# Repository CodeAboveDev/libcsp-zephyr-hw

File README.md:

# Cubesat Space Protocol with Zephyr - Hardware
PCB schematic and layout for stacking WeAct BlackPill boards.

Software: https://github.com/CodeAboveDev/libcsp-zephyr

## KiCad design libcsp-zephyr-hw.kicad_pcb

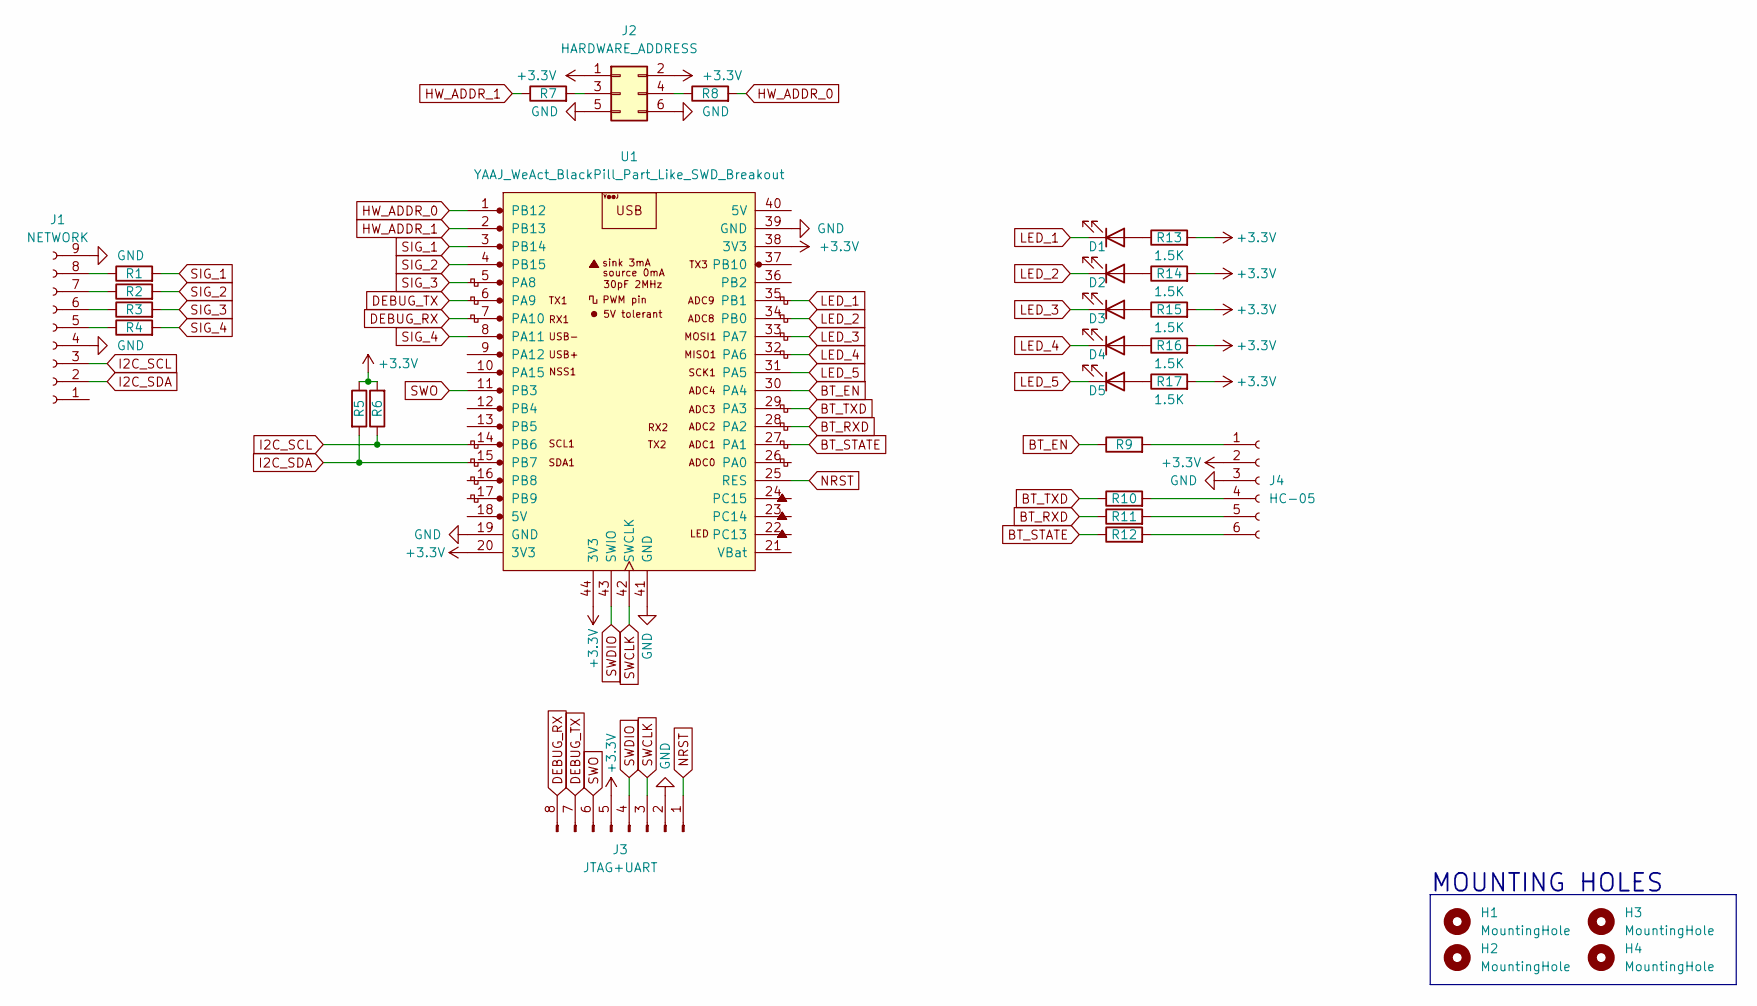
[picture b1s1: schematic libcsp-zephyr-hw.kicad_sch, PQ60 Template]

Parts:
D1, D2, D3, D4, D5: LED; LED_0805_2012Metric
H1, H2, H3, H4: MountingHole; MountingHole_2.2mm_M2_Pad_Via
J1: NETWORK; PinSocket_1x09_P2.54mm_Vertical
J2: HARDWARE_ADDRESS; PinHeader_2x03_P2.54mm_Horizontal
J3: JTAG+UART; PinHeader_1x08_P2.54mm_Horizontal
J4: HC-05; PinSocket_1x06_P2.54mm_Vertical
R1, R2, R3, R4, R5, R6, R7, R8, R9, R10, R11, R12: R; R_0805_2012Metric
R13, R14, R15, R16, R17: 1.5K; R_0805_2012Metric
U1: YAAJ_WeAct_BlackPill_Part_Like_SWD_Breakout; YAAJ_WeAct_BlackPill_SWD_2

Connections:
+3.3V: J2.1, J2.2, J3.5, J4.2, R5.1, R6.2, R13.2, R14.2, R15.2, R16.2, R17.2, U1.20 (3V3), U1.38 (3V3), U1.44 (3V3)
BT_EN: R9.1, U1.30 (PA4)
BT_RXD: R11.1, U1.28 (PA2)
BT_STATE: R12.1, U1.27 (PA1)
BT_TXD: R10.1, U1.29 (PA3)
DEBUG_RX: J3.8, U1.7 (PA10)
DEBUG_TX: J3.7, U1.6 (PA9)
GND: J1.4, J1.9, J2.5, J2.6, J3.2, J4.3, U1.19 (GND), U1.39 (GND), U1.41 (GND)
HW_ADDR_0: R8.2, U1.1 (PB12)
HW_ADDR_1: R7.1, U1.2 (PB13)
I2C_SCL: J1.3, R6.1, U1.14 (PB6)
I2C_SDA: J1.2, R5.2, U1.15 (PB7)
LED_1: D1.1 (K), U1.35 (PB1)
LED_2: D2.1 (K), U1.34 (PB0)
LED_3: D3.1 (K), U1.33 (PA7)
LED_4: D4.1 (K), U1.32 (PA6)
LED_5: D5.1 (K), U1.31 (PA5)
NRST: J3.1, U1.25 (RES)
unnamed: D1.2 (A), R13.1
unnamed: D2.2 (A), R14.1
unnamed: D3.2 (A), R15.1
unnamed: D4.2 (A), R16.1
unnamed: D5.2 (A), R17.1
unnamed: J1.5, R4.1
unnamed: J1.6, R3.1
unnamed: J1.7, R2.1
unnamed: J1.8, R1.1
unnamed: J2.3, R7.2
unnamed: J2.4, R8.1
unnamed: J4.1, R9.2
unnamed: J4.4, R10.2
unnamed: J4.5, R11.2
unnamed: J4.6, R12.2
SIG_1: R1.2, U1.3 (PB14)
SIG_2: R2.2, U1.4 (PB15)
SIG_3: R3.2, U1.5 (PA8)
SIG_4: R4.2, U1.8 (PA11)
SWCLK: J3.3, U1.42 (SWCLK)
SWDIO: J3.4, U1.43 (SWIO)
SWO: J3.6, U1.11 (PB3)

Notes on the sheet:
MOUNTING HOLES

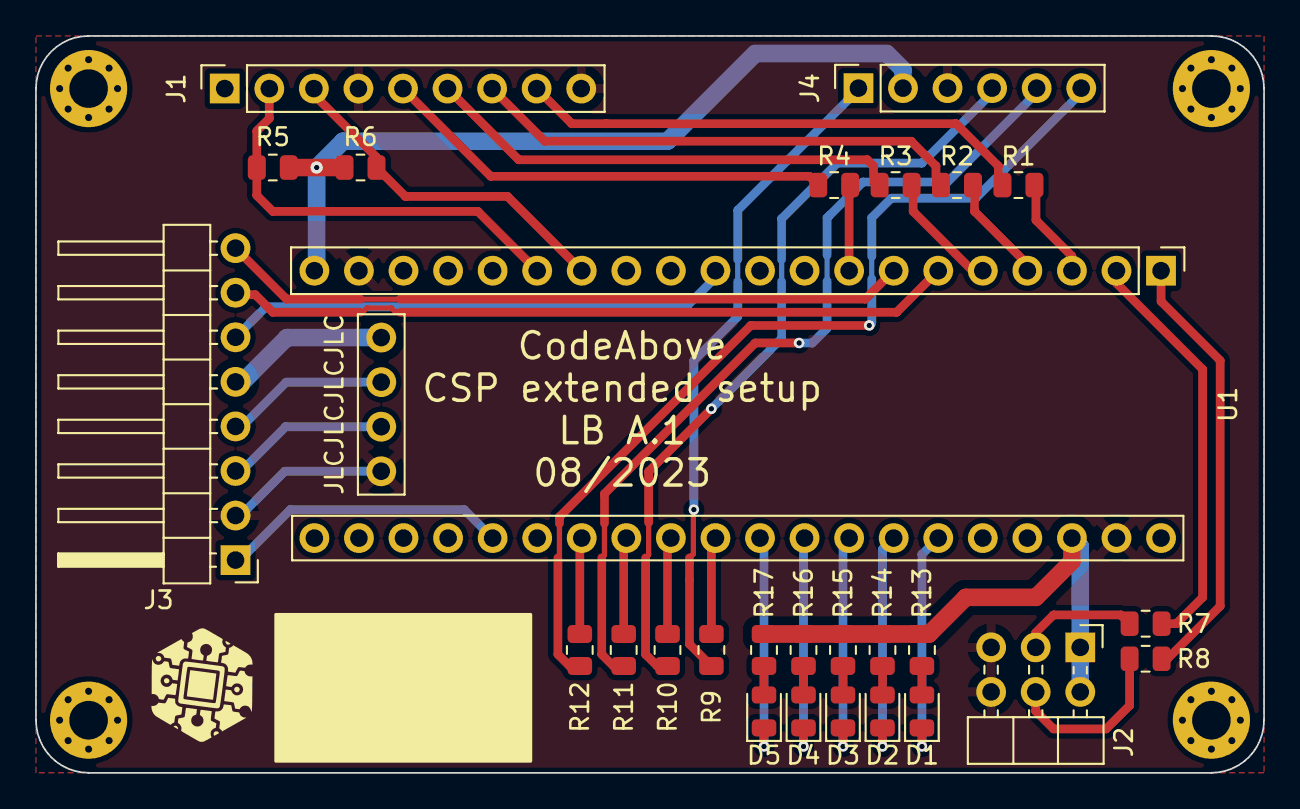
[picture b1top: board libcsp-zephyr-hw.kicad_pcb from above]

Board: 2 copper layers, 70.0 x 42.0 mm, 31 parts (0 on the bottom side), 40 nets.

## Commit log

2023-09-01 Board revision A.1 with gerber
2023-11-03 Add some resistor values
